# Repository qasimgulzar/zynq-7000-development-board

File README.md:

# Zynq-7000 Development Board (KiCad project)

This repository contains the KiCad project files for a Zynq-7000 development board. The design provides the typical power rails and connectors needed to evaluate and develop with Zynq-7000 series devices.

Files of interest
- `zynq-7000-development-board.kicad_sch` - top-level schematic
- `power_rails.kicad_sch` - power supply sheets and regulator circuitry
- `zynq-7000-development-board.kicad_pcb` - PCB layout
- `exports/` - generated Gerber/DRL and manufacturing outputs

Power rails

The schematic (`power_rails.kicad_sch`) defines the following primary nets and rails used by the board. These names come directly from global labels and regulator parts found in the power sheet.

- 12V (input)
  - Primary input rail; a barrel jack with internal switch (`J1`) is present in the power sheet. Global labels named `12V` route this input around the power page.

- 5V
  - Generated by an AMS1117-5.0 regulator (part: `U5`). Global label: `5V`.

- 3.3V
  - Generated by an AMS1117-3.3 regulator (part: `U4`). Global label: `3.3V`.

- 1.8V
  - Generated by an AMS1117-1.8 regulator (part: `U1`). Global label: `1.8V`.

- 1.5V
  - Several AMS1117-1.5 regulators are present (parts: `U2`, `U3`, `U6`, etc.) producing `1.5V` rails where required. Global labels: `1.5V`.

- 1.25V and 1.0V
  - Net labels `1.25V` and `1V` appear in the power sheet (these are typically used by certain Zynq fabric or memory rails). No dedicated fixed AMS1117 parts for 1.25V/1.0V are present in this power sheet; verify whether those rails are supplied by separate on-board regulators, programmable regulators on another sheet, or expected from an external source. Treat these rails as critical for the Zynq core/memory and confirm their sourcing before powering the device.

- GND (Ground)
  - Global `GND` power symbols and multiple PWR_FLAG symbols are present to indicate power sources for ERC.

Notes about components and decoupling
- Several decoupling/bulk capacitors (example: `C1`..`C6`) with value `22uF` are placed near regulators and nets.
- A small set of resistors (e.g., `R1`, `R2`, `R3`, `R4`) appear in the power sheet for sensing, pull-ups/pull-downs or divider uses. Values seen include `5K`, `10K`, `2K`.
- Power markers (`PWR_FLAG`) are included to inform KiCad ERC about power sources.

Important cautions and checklist before powering
- Confirm sources for `1.25V` and `1.0V` nets — the `power_rails.kicad_sch` file contains labeled nets but no obvious fixed regulators for those voltages in the same file. If these rails are required by the Zynq device (VCCINT, memory rails, etc.), supply them from a verified regulator or set the jumpers/configuration accordingly.
- Verify regulator input voltage and power dissipation: some linear regulators (AMS1117 family) are used; if fed from 12V they will dissipate significant power when dropping to lower voltages. Consider switching regulators if heat or efficiency is a concern.
- Run ERC (Electrical Rules Check) in KiCad and inspect inter-sheet connections before build.

How to use this repo
1. Open the project in KiCad 7 (or compatible Eeschema / PCBNew version).
2. Run ERC on each schematic sheet and inspect power net connectivity.
3. Review the PCB layout and keepout areas located in `zynq-7000-development-board.kicad_pcb`.
4. Use the `exports/` folder for the Gerbers and drill files when ready to manufacture.

Notes / next steps (recommended)
- Add explicit documentation in the schematics or a dedicated README section about where `1.25V` and `1V` are generated from (if from an external module or another schematic sheet).
- Consider adding a power-budget calculation and regulator thermal check to the repository.

If you'd like, I can also:
- Add a short power-budget spreadsheet to the repo.
- Scan other schematic sheets to find where `1.25V`/`1V` are actually generated if they are present on different pages.

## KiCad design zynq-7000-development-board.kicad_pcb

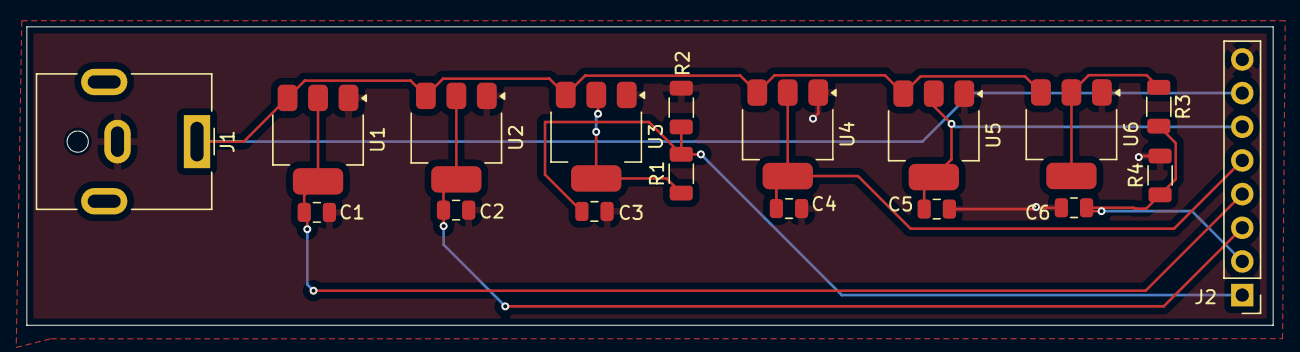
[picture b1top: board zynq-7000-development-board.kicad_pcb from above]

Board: 2 copper layers, 94.0 x 22.5 mm, 18 parts (0 on the bottom side), 10 nets.

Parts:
C1, C2, C3, C4, C5, C6: 22uF; C_0805_2012Metric
J1: Barrel_Jack_Switch; BarrelJack_CUI_PJ-063AH_Horizontal
J2: Conn_01x08_Pin; PinHeader_1x08_P2.54mm_Vertical
R1: 5K; R_1206_3216Metric
R2, R4: 10K; R_1206_3216Metric
R3: 2K; R_1206_3216Metric
U1: AMS1117-1.8; SOT-223-3_TabPin2
U2, U3, U6: AMS1117-1.5; SOT-223-3_TabPin2
U4: AMS1117-3.3; SOT-223-3_TabPin2
U5: AMS1117-5.0; SOT-223-3_TabPin2

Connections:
1.5V: C2.1, J2.3, U2.2 (VO)
1.8V: C1.1, J2.4, U1.2 (VO)
1.25V: C6.1, J2.2, R3.2, R4.1
1V: C3.1, J2.1, R1.2, R2.1
3.3V: C4.1, J2.5, U4.2 (VO)
5V: C5.1, J2.6, U5.2 (VO)
12V: J1.1, J2.7, U1.3 (VI), U2.3 (VI), U3.3 (VI), U4.3 (VI), U5.3 (VI), U6.3 (VI)
GND: C1.2, C2.2, C3.2, C4.2, C5.2, C6.2, J1.2, J2.8, R2.2, R4.2, U1.1 (GND), U2.1 (GND), U3.1 (GND), U4.1 (GND), U5.1 (GND), U6.1 (GND)
unnamed: R1.1, U3.2 (VO)
unnamed: R3.1, U6.2 (VO)

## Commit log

2025-11-02 INIT - Zynq-7000 power rails
